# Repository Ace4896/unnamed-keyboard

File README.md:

# Unnamed Keyboard

A (work-in-progress) keyboard.

## Parts

The PCB is built around the following components

- [RP2040 Microcontroller](https://www.raspberrypi.com/documentation/microcontrollers/rp2040.html)
- [Kailh CPG151101S11 Hotswap Sockets](http://www.kailh.com/en/Products/Ks/HPC/883.html)
- [EC11E Rotary Encoder](https://tech.alpsalpine.com/e/products/category/encorder/sub/01/series/ec11e/)
  - Any EC11E rotary encoder will do as long as it has a push-on switch (i.e. it can be pressed down)
  - I used the [Alps EC11E15244G1](https://tech.alpsalpine.com/e/products/detail/EC11E15244G1/)
- ... remaining parts to be determined

## Useful Resources

This is my first attempt at designing anything keyboard related, and I've been referring to various guides online to come up with these designs. I've listed some of the resources I've used below:

- [Keyboard Layout Editor (KLE)](http://www.keyboard-layout-editor.com/) for designing and exporting the layout
- **PCB Design**
  - [Noah Kiser](https://www.youtube.com/@noahkiser)'s PCB design videos on YouTube
  - [ebastler/marbastlib](https://github.com/ebastler/marbastlib) KiCAD library with various keyboard-related parts and footprints
  - [zykrah/kicad-kle-placer](https://github.com/zykrah/kicad-kle-placer) KiCAD plugin for placing switch footprints based on a KLE

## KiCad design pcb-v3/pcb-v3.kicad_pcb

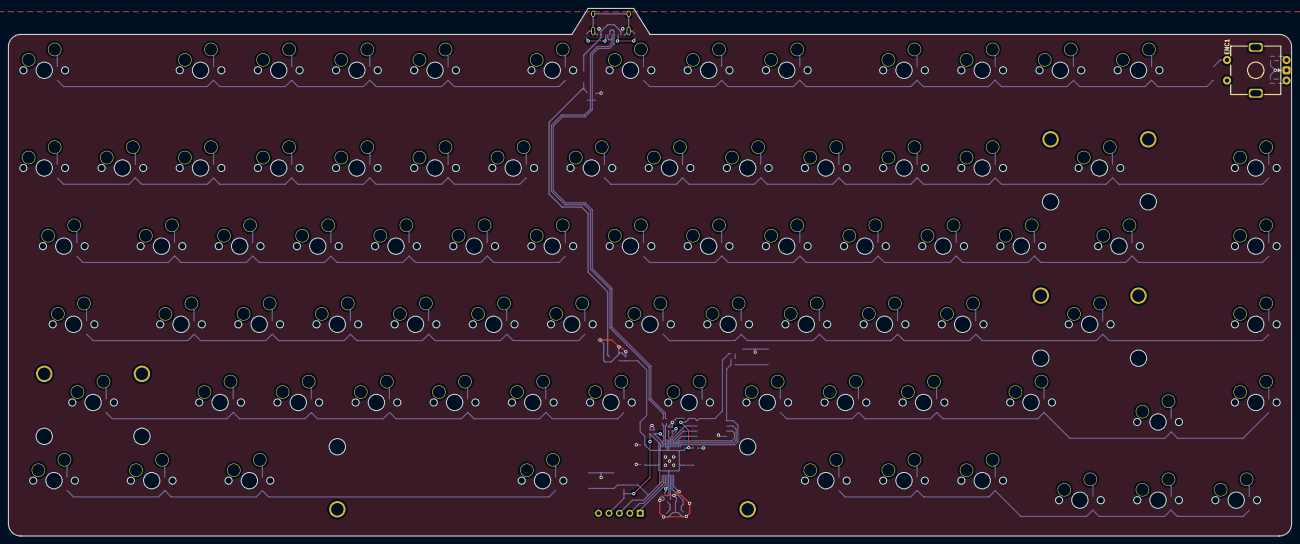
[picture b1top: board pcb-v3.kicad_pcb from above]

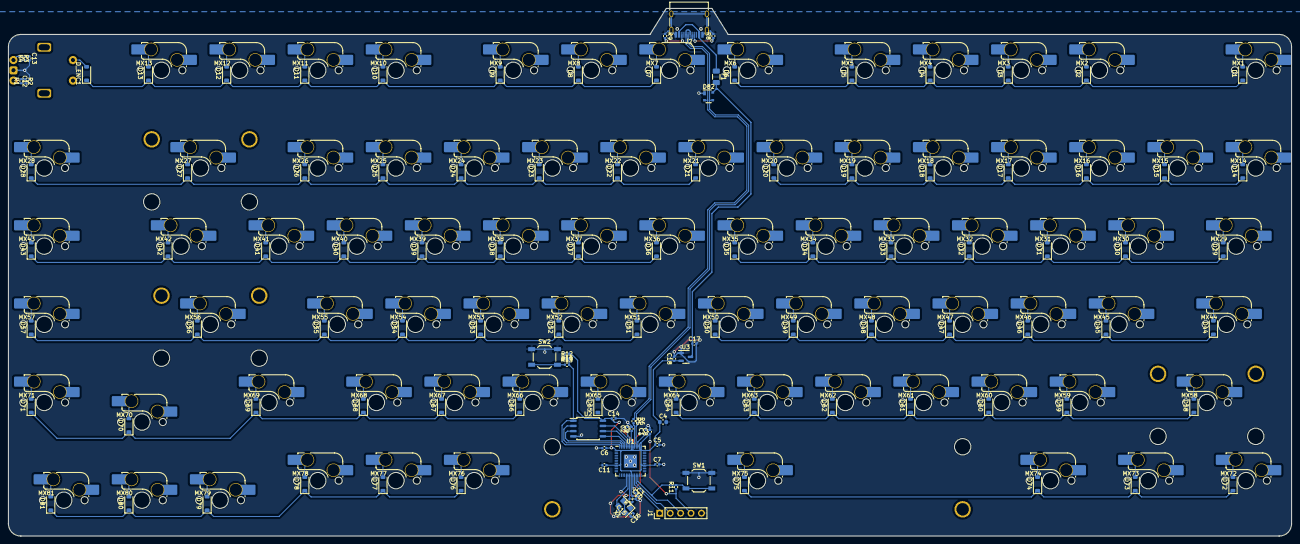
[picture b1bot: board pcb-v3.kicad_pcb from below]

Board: 2 copper layers, 312.7 x 128.6 mm, 209 parts (208 on the bottom side), 134 nets.

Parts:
C1, C5, C14, C17, C18: 1u; C_0402_1005Metric
C2, C3, C6, C7, C8, C9, C10, C11: 100n; C_0402_1005Metric
C4: 10u; C_0603_1608Metric
C12, C13: 10n; C_0402_1005Metric
C15, C16: 22p; C_0402_1005Metric
D1, D2, D3, D4, D5, D6, D7, D8, D9, D10, D11, D12, D13, D14, D15, D16, D17, D18, D19, D20, D21, D22, D23, D24, D25, D26, D27, D28, D29, D30, D31, D32, D33, D34, D35, D36, D37, D38, D39, D40, D41, D42, D43, D44, D45, D46, D47, D48, D49, D50, D51, D52, D53, D54, D55, D56, D57, D58, D59, D60, D61, D62, D63, D64, D65, D66, D67, D68, D69, D70, D71, D72, D73, D74, D75, D76, D77, D78, D79, D80, D81: D_Small; D_SOD-123
D82: PRTR5V0U2X; SOT-143
D_ENC1: D_Small; D_SOD-123
ENC1: EC11E15244G1; ROT_Alps_EC11E-Switch
F1: 500mA; Fuse_1206_3216Metric
J1: Conn_01x05; PinHeader_1x05_P2.54mm_Vertical
J2: USB_C_Receptacle_USB2.0; USB_C_Receptacle_HRO_TYPE-C-31-M-12
MX1, MX2, MX3, MX4, MX5, MX6, MX7, MX8, MX9, MX10, MX11, MX12, MX13, MX14, MX15, MX16, MX17, MX18, MX19, MX20, MX21, MX22, MX23, MX24, MX25, MX26, MX27, MX28, MX30, MX31, MX32, MX33, MX34, MX35, MX36, MX37, MX38, MX39, MX40, MX41, MX43, MX45, MX46, MX47, MX48, MX49, MX50, MX51, MX52, MX53, MX54, MX55, MX56, MX57, MX58, MX59, MX60, MX61, MX62, MX63, MX64, MX65, MX66, MX67, MX68, MX70, MX71, MX75, MX76, MX77, MX78, MX79, MX80, MX81: MX_SW_HS; SW_MX_HS_1u
MX29, MX42: MX_SW_HS; SW_MX_HS_1.5u
MX44, MX69: MX_SW_HS; SW_MX_HS_1.75u
MX72, MX73, MX74: MX_SW_HS; SW_MX_HS_1.25u
R1, R2, R3, R4, R8, R9, R10, R11, R12: 5k1; R_0402_1005Metric
R5, R6: 27; R_0402_1005Metric
R7, R13: 1k; R_0402_1005Metric
S1: LShift; STAB_MX_P_2.25u
S2: Space; STAB_MX_P_6.25u
S3: Backspace; STAB_MX_P_2u
S4: Enter; STAB_MX_P_2.25u
SW1, SW2: SW_Push; SW_SPST_TL3342
U1: RP2040; QFN-56-1EP_7x7mm_P0.4mm_EP3.2x3.2mm
U2: W25Q128JVS; SOIC-8_5.23x5.23mm_P1.27mm
U3: XC6206P332MR; SOT-23-3
X1: 12MHz; Crystal_SMD_3225-4Pin_3.2x2.5mm

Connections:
+1V1: C1.1, C2.1, C3.1, U1.23 (DVDD), U1.45 (VREG_VOUT), U1.50 (DVDD)
+3V3: C4.1, C5.1, C6.1, C7.1, C8.1, C9.1, C10.1, C11.1, C14.1, C18.1, J1.4, R10.1, R11.1, U1.1 (IOVDD), U1.10 (IOVDD), U1.22 (IOVDD), U1.33 (IOVDD), U1.42 (IOVDD), U1.43 (ADC_AVDD), U1.44 (VREG_IN), U1.48 (USB_VDD), U1.49 (IOVDD), U2.8 (VCC), U3.2 (VO)
+5V: C17.1, D82.4 (VCC), F1.2, U3.3 (VI)
COL0: MX1.1, MX14.1, MX29.1, MX44.1, MX58.1, MX72.1
COL1: MX2.1, MX15.1, MX30.1, MX45.1, MX59.1, MX73.1
COL2: MX3.1, MX16.1, MX31.1, MX46.1, MX60.1, MX74.1
COL3: MX4.1, MX17.1, MX32.1, MX47.1, MX61.1
COL4: MX5.1, MX18.1, MX33.1, MX48.1, MX62.1
COL5: MX6.1, MX19.1, MX34.1, MX49.1, MX63.1, MX75.1
COL6: MX7.1, MX20.1, MX35.1, MX50.1, MX64.1
COL7: MX8.1, MX21.1, MX36.1, MX51.1, MX65.1
COL8: MX9.1, MX22.1, MX37.1, MX52.1, MX66.1, MX76.1
COL9: MX10.1, MX23.1, MX38.1, MX53.1, MX67.1, MX77.1
COL10: MX11.1, MX24.1, MX39.1, MX54.1, MX68.1, MX78.1
COL11: MX12.1, MX25.1, MX40.1, MX55.1, MX69.1, MX79.1
COL12: MX13.1, MX26.1, MX41.1, MX56.1, MX70.1, MX80.1
COL13: MX27.1, MX42.1, MX81.1
COL14: ENC1.S2, MX28.1, MX43.1, MX57.1, MX71.1
D+: D82.2 (I/O1), J2.A6 (D+), J2.B6 (D+), R5.1
D-: D82.3 (I/O2), J2.A7 (D-), J2.B7 (D-), R6.1
ENC_A: C12.1, R2.2
ENC_B: C13.1, R4.2
GND: C1.2, C2.2, C3.2, C4.2, C5.2, C6.2, C7.2, C8.2, C9.2, C10.2, C11.2, C12.2, C13.2, C14.2, C15.2, C16.2, C17.2, C18.2, D82.1 (GND), ENC1.C, J1.5, J2.A1 (GND), J2.A12 (GND), J2.B1 (GND), J2.B12 (GND), J2.S1 (SHIELD), R8.2, R9.1, SW1.1, SW2.1, U1.19 (TESTEN), U1.57 (GND), U2.4 (GND), U3.1 (GND), X1.2, X1.4
unnamed: C16.1, R7.1, X1.1
unnamed: D1.2 (A), MX1.2
unnamed: D2.2 (A), MX2.2
unnamed: D3.2 (A), MX3.2
unnamed: D4.2 (A), MX4.2
unnamed: D5.2 (A), MX5.2
unnamed: D6.2 (A), MX6.2
unnamed: D7.2 (A), MX7.2
unnamed: D8.2 (A), MX8.2
unnamed: D9.2 (A), MX9.2
unnamed: D10.2 (A), MX10.2
unnamed: D11.2 (A), MX11.2
unnamed: D12.2 (A), MX12.2
unnamed: D13.2 (A), MX13.2
unnamed: D14.2 (A), MX14.2
unnamed: D15.2 (A), MX15.2
unnamed: D16.2 (A), MX16.2
unnamed: D17.2 (A), MX17.2
unnamed: D18.2 (A), MX18.2
unnamed: D19.2 (A), MX19.2
unnamed: D20.2 (A), MX20.2
unnamed: D21.2 (A), MX21.2
unnamed: D22.2 (A), MX22.2
unnamed: D23.2 (A), MX23.2
unnamed: D24.2 (A), MX24.2
unnamed: D25.2 (A), MX25.2
unnamed: D26.2 (A), MX26.2
unnamed: D27.2 (A), MX27.2
unnamed: D28.2 (A), MX28.2
unnamed: D29.2 (A), MX29.2
unnamed: D30.2 (A), MX30.2
unnamed: D31.2 (A), MX31.2
unnamed: D32.2 (A), MX32.2
unnamed: D33.2 (A), MX33.2
unnamed: D34.2 (A), MX34.2
unnamed: D35.2 (A), MX35.2
unnamed: D36.2 (A), MX36.2
unnamed: D37.2 (A), MX37.2
unnamed: D38.2 (A), MX38.2
unnamed: D39.2 (A), MX39.2
unnamed: D40.2 (A), MX40.2
unnamed: D41.2 (A), MX41.2
unnamed: D42.2 (A), MX42.2
unnamed: D43.2 (A), MX43.2
unnamed: D44.2 (A), MX44.2
unnamed: D45.2 (A), MX45.2
unnamed: D46.2 (A), MX46.2
unnamed: D47.2 (A), MX47.2
unnamed: D48.2 (A), MX48.2
unnamed: D49.2 (A), MX49.2
unnamed: D50.2 (A), MX50.2
unnamed: D51.2 (A), MX51.2
unnamed: D52.2 (A), MX52.2
unnamed: D53.2 (A), MX53.2
unnamed: D54.2 (A), MX54.2
unnamed: D55.2 (A), MX55.2
unnamed: D56.2 (A), MX56.2
unnamed: D57.2 (A), MX57.2
unnamed: D58.2 (A), MX58.2
unnamed: D59.2 (A), MX59.2
unnamed: D60.2 (A), MX60.2
unnamed: D61.2 (A), MX61.2
unnamed: D62.2 (A), MX62.2
unnamed: D63.2 (A), MX63.2
unnamed: D64.2 (A), MX64.2
unnamed: D65.2 (A), MX65.2
unnamed: D66.2 (A), MX66.2
unnamed: D67.2 (A), MX67.2
unnamed: D68.2 (A), MX68.2
unnamed: D69.2 (A), MX69.2
unnamed: D70.2 (A), MX70.2
unnamed: D71.2 (A), MX71.2
unnamed: D72.2 (A), MX72.2
unnamed: D73.2 (A), MX73.2
unnamed: D74.2 (A), MX74.2
unnamed: D75.2 (A), MX75.2
unnamed: D76.2 (A), MX76.2
unnamed: D77.2 (A), MX77.2
unnamed: D78.2 (A), MX78.2
unnamed: D79.2 (A), MX79.2
unnamed: D80.2 (A), MX80.2
unnamed: D81.2 (A), MX81.2
unnamed: D_ENC1.2 (A), ENC1.S1
unnamed: ENC1.A, R1.1
unnamed: ENC1.B, R3.1
unnamed: J2.A5 (CC1), R8.1
unnamed: J2.B5 (CC2), R9.2
unnamed: R1.2, R2.1
unnamed: R3.2, R4.1
unnamed: R10.2, R12.1
unnamed: R13.1, SW2.2
unnamed: R6.2, U1.46 (USB_DM)
unnamed: R5.2, U1.47 (USB_DP)
Q_CLK: U1.52 (QSPI_SCLK), U2.6 (CLK)
Q_IO0: U1.53 (QSPI_SD0), U2.5 (DI(IO0))
Q_IO1: U1.55 (QSPI_SD1), U2.2 (DO(IO1))
Q_IO2: U1.54 (QSPI_SD2), U2.3 (IO2)
Q_IO3: U1.51 (QSPI_SD3), U2.7 (IO3)
Q_SEL: R12.2, R13.2, U1.56 (QSPI_SS), U2.1 (~CS)
RESET: J1.3, R11.2, SW1.2, U1.26 (RUN)
ROW0: D1.1 (K), D2.1 (K), D3.1 (K), D4.1 (K), D5.1 (K), D6.1 (K), D7.1 (K), D8.1 (K), D9.1 (K), D10.1 (K), D11.1 (K), D12.1 (K), D13.1 (K), D_ENC1.1 (K)
ROW1: D14.1 (K), D15.1 (K), D16.1 (K), D17.1 (K), D18.1 (K), D19.1 (K), D20.1 (K), D21.1 (K), D22.1 (K), D23.1 (K), D24.1 (K), D25.1 (K), D26.1 (K), D27.1 (K), D28.1 (K)
ROW2: D29.1 (K), D30.1 (K), D31.1 (K), D32.1 (K), D33.1 (K), D34.1 (K), D35.1 (K), D36.1 (K), D37.1 (K), D38.1 (K), D39.1 (K), D40.1 (K), D41.1 (K), D42.1 (K), D43.1 (K)
ROW3: D44.1 (K), D45.1 (K), D46.1 (K), D47.1 (K), D48.1 (K), D49.1 (K), D50.1 (K), D51.1 (K), D52.1 (K), D53.1 (K), D54.1 (K), D55.1 (K), D56.1 (K), D57.1 (K)
ROW4: D58.1 (K), D59.1 (K), D60.1 (K), D61.1 (K), D62.1 (K), D63.1 (K), D64.1 (K), D65.1 (K), D66.1 (K), D67.1 (K), D68.1 (K), D69.1 (K), D70.1 (K), D71.1 (K)
ROW5: D72.1 (K), D73.1 (K), D74.1 (K), D75.1 (K), D76.1 (K), D77.1 (K), D78.1 (K), D79.1 (K), D80.1 (K), D81.1 (K)
SWC: J1.1, U1.24 (SWCLK)
SWD: J1.2, U1.25 (SWD)
VBUS: F1.1, J2.A4 (VBUS), J2.A9 (VBUS), J2.B4 (VBUS), J2.B9 (VBUS)
XIN: C15.1, U1.20 (XIN), X1.3
XOUT: R7.2, U1.21 (XOUT)

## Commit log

2023-09-16 feat: initial commit
2023-09-16 docs: add kle
2023-09-16 feat: add kle ideas and rename project
2023-09-16 feat: setup most of ansi mx pcb still need to setup the key matrix and begin routing.
2023-09-16 docs: I have -> I've
2023-09-17 feat: add rotary encoder
2023-09-17 feat: add some of the confirmed parts
2023-09-17 feat: initial key matrix + encoder debounce
2023-09-17 refactor: remove f13 (to make space for usb port)
2023-09-17 refactor: use molex instead of jst for daughterboard connector
2023-09-17 refactor: remove daughterboard connector
2023-09-17 feat: route everything but encoder and matrix
2023-09-19 feat: add auto-generated plate from swillkb
2023-09-21 feat: initial attempt at adding usb hub
2023-09-22 feat: attempt at using ch334
2023-09-22 feat: another attempt at wiring pcb using middle mounted usb-c this time round.
2023-09-22 feat: attempt at routing rows
